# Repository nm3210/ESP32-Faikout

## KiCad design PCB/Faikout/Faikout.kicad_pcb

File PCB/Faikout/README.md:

# Faikout

## Trademark

This project is subject to the licence in the LICENCE file, and even if that says it is an open source project, you cannot sell boards or cases bearing the Andrews & Arnold Ltd name, the A&A logo, the registered trademark AJK logo or other registered trademarks, or any GS1 allocated EANs/barcode assigned to Andrews & Arnold Ltd.

## PCB Designs

These files are for use with [KiCAD](https://www.kicad.org).

- [Faikout](Faikout.kicad_pro)

## 3D

3D case designs are normally automatically created from the PCB so as to ensure correct details and placement of apertures, etc.

|Design|Bottom|Top|Combined|
|------|------|---|--------|
|Faikout||||

## PCB Images

---

*Auto generated README.md 2026-04-05T14:23:08*

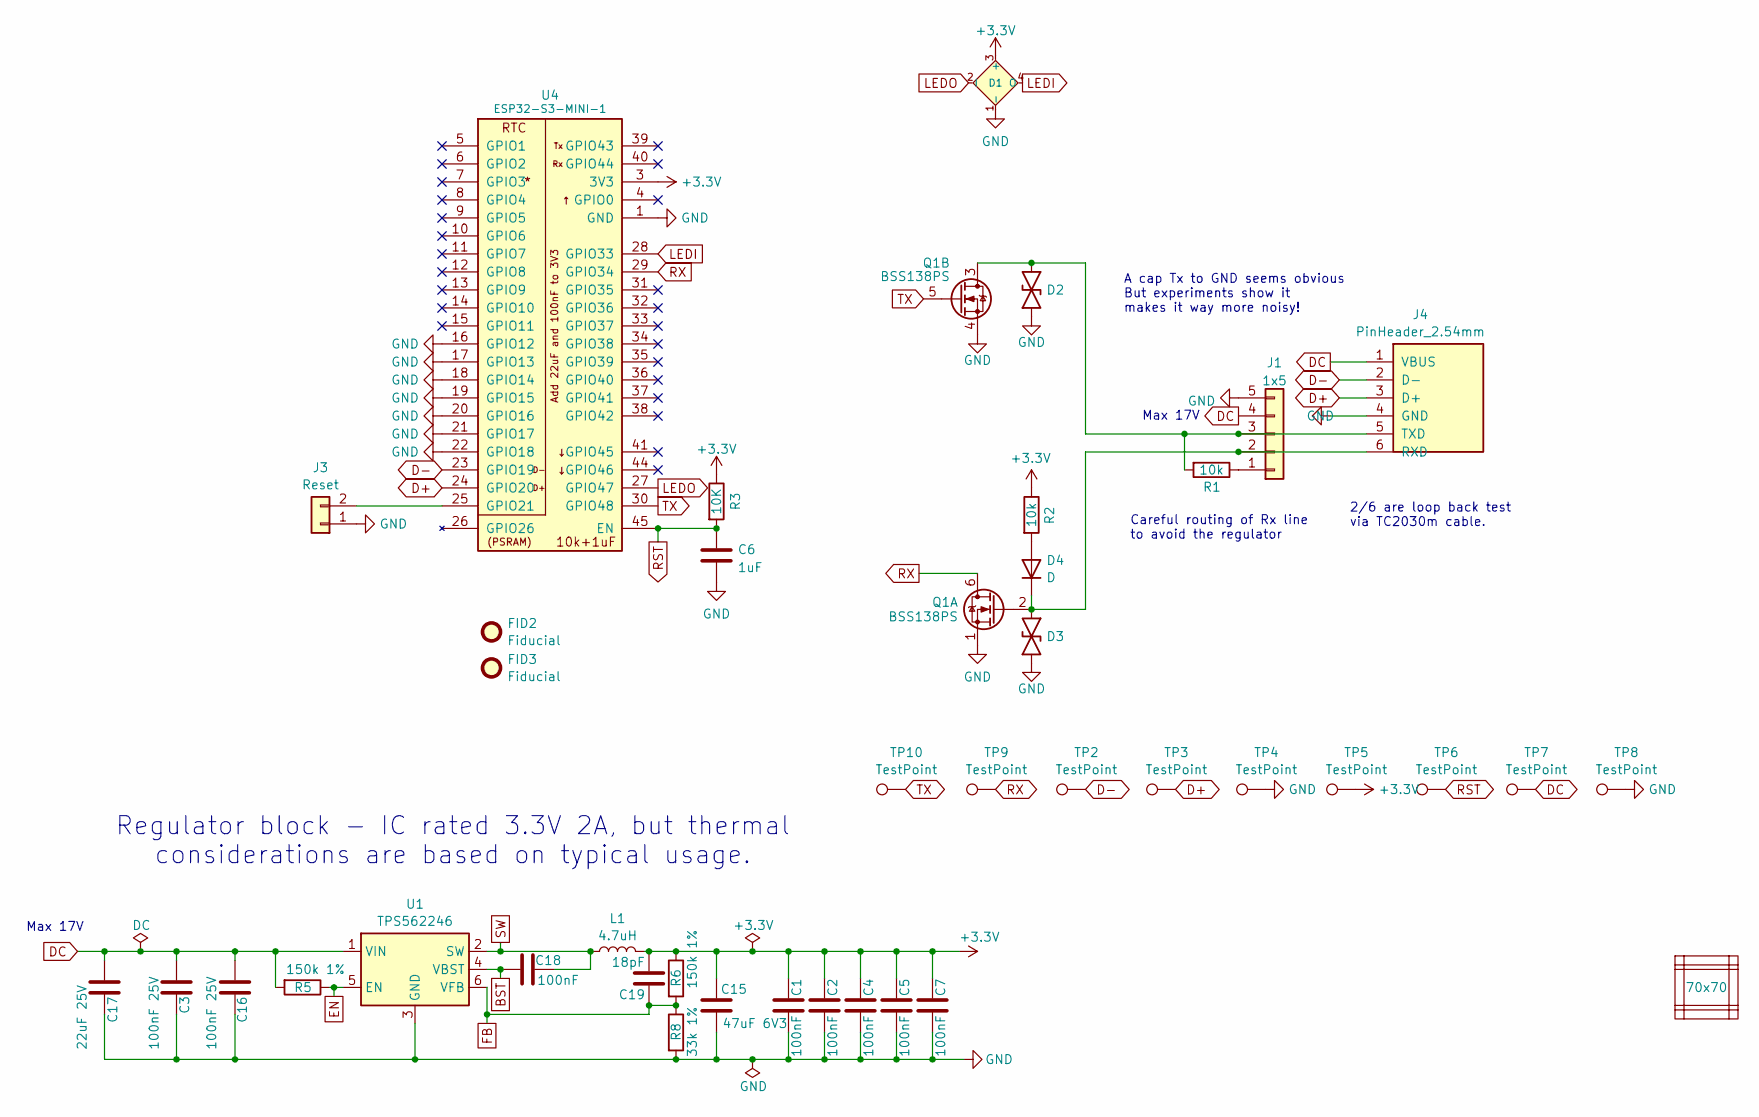
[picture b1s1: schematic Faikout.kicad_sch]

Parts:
C1, C2, C4, C5, C7, C18: 100nF; C_0201; MPN C76934
C3, C16: 100nF 25V; C_0402; MPN C56392
C6: 1uF; C_0201
C15: 47uF 6V3; C_0805; MPN C16780
C17: 22uF 25V; C_0805; MPN C45783
C19: 18pF; C_0201; MPN C62164
D1: XL-1615RGBC-2812B; SMD1615; MPN C5349954
D2, D3: DFN1006-2L; MPN C5137770
D4: D; D_0402; MPN C28642302
FID2, FID3: Fiducial; Fiducial_1mm_Mask2mm
J1: 1x5; JST_EH_S5B-EH_1x05_P2.50mm_Horizontal; MPN C265103
J3: Reset; AA-Pad
J4: PinHeader_2.54mm; PinHeader_1x06_P2.54mm_Vertical
L1: 4.7uH; L_5x5; MPN C307876
PCB1: 70x70; PCB7070
Q1: BSS138PS; SOT-363_SC-70-6; MPN C193381
R1, R2: 10k; R_0201; MPN C106225
R3: 10K; R_0201; MPN C106225
R5, R6: 150k 1%; R_0201; MPN C310173
R8: 33k 1%; R_0201; MPN C320835
TP2, TP3, TP4, TP5, TP6, TP7, TP8, TP9, TP10: TestPoint; PAD-2mm
U1: TPS562246; SOT-5x3-6; MPN C41833479
U4: ESP32-S3-MINI-1; MPN C3013941
V1, V2, V3, V4, V5, V6: VCUT70N

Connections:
+3.3V: C1.2, C2.2, C4.2, C5.2, C7.2, C15.1, C19.2, D1.3 (+), L1.2, R2.1, R3.1, R6.1, TP5.1, U4.3 (3V3)
BST: C18.1, U1.4 (VBST)
D+: J4.3 (D+), TP3.1, U4.24 (GPIO20); also elsewhere on the board
D-: J4.2 (D-), TP2.1, U4.23 (GPIO19); also elsewhere on the board
DC: C3.1, C16.1, C17.1, J1.4, J4.1 (VBUS), R5.2, TP7.1, U1.1 (VIN); also elsewhere on the board
EN: R5.1, U1.5 (EN)
FB: C19.1, R6.2, R8.1, U1.6 (VFB)
GND: C1.1, C2.1, C3.2, C4.1, C5.1, C6.2, C7.1, C15.2, C16.2, C17.2, D1.1 (-), D2.1, D3.1, J1.5, J3.1, J4.4 (GND), Q1.1 (SN), Q1.4 (DP), R8.2, TP4.1, TP8.1, U1.3 (GND), U4.1 (GND), U4.2 (GND), U4.16 (GPIO12), U4.17 (GPIO13), U4.18 (GPIO14), U4.19 (GPIO15), U4.20 (GPIO16), U4.21 (GPIO17), U4.22 (GPIO18), U4.42 (GND), U4.43 (GND), U4.46 (GND), U4.47 (GND), U4.48 (GND), U4.49 (GND), U4.50 (GND), U4.51 (GND), U4.52 (GND), U4.53 (GND), U4.54 (GND), U4.55 (GND), U4.56 (GND), U4.57 (GND), U4.58 (GND), U4.59 (GND), U4.60 (GND), U4.61 (GND), U4.62 (GND), U4.63 (GND), U4.64 (GND), U4.65 (GND); also elsewhere on the board
LEDI: D1.4 (O), U4.28 (GPIO33)
LEDO: D1.2 (I), U4.27 (GPIO47)
unnamed: D4.2 (A), R2.2
unnamed 11: D3.2, D4.1 (K), J1.2, J4.6 (RXD), Q1.2 (GN); also elsewhere on the board
unnamed: J1.1, R1.1
unnamed 13: D2.2, J1.3, J4.5 (TXD), Q1.3 (SP), R1.2; also elsewhere on the board
unnamed: J3.2, U4.25 (GPIO21)
RST: C6.1, R3.2, TP6.1, U4.45 (EN)
RX: Q1.6 (DN), TP9.1, U4.29 (GPIO34)
SW: C18.2, L1.1, U1.2 (SW)
TX: Q1.5 (GP), TP10.1, U4.30 (GPIO48)

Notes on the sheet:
Max 17V
Careful routing of Rx line to avoid the regulator
2/6 are loop back test via TC2030m cable.
A cap Tx to GND seems obvious But experiments show it makes it way more noisy!
Regulator block - IC rated 3.3V 2A, but thermal considerations are based on typical usage.

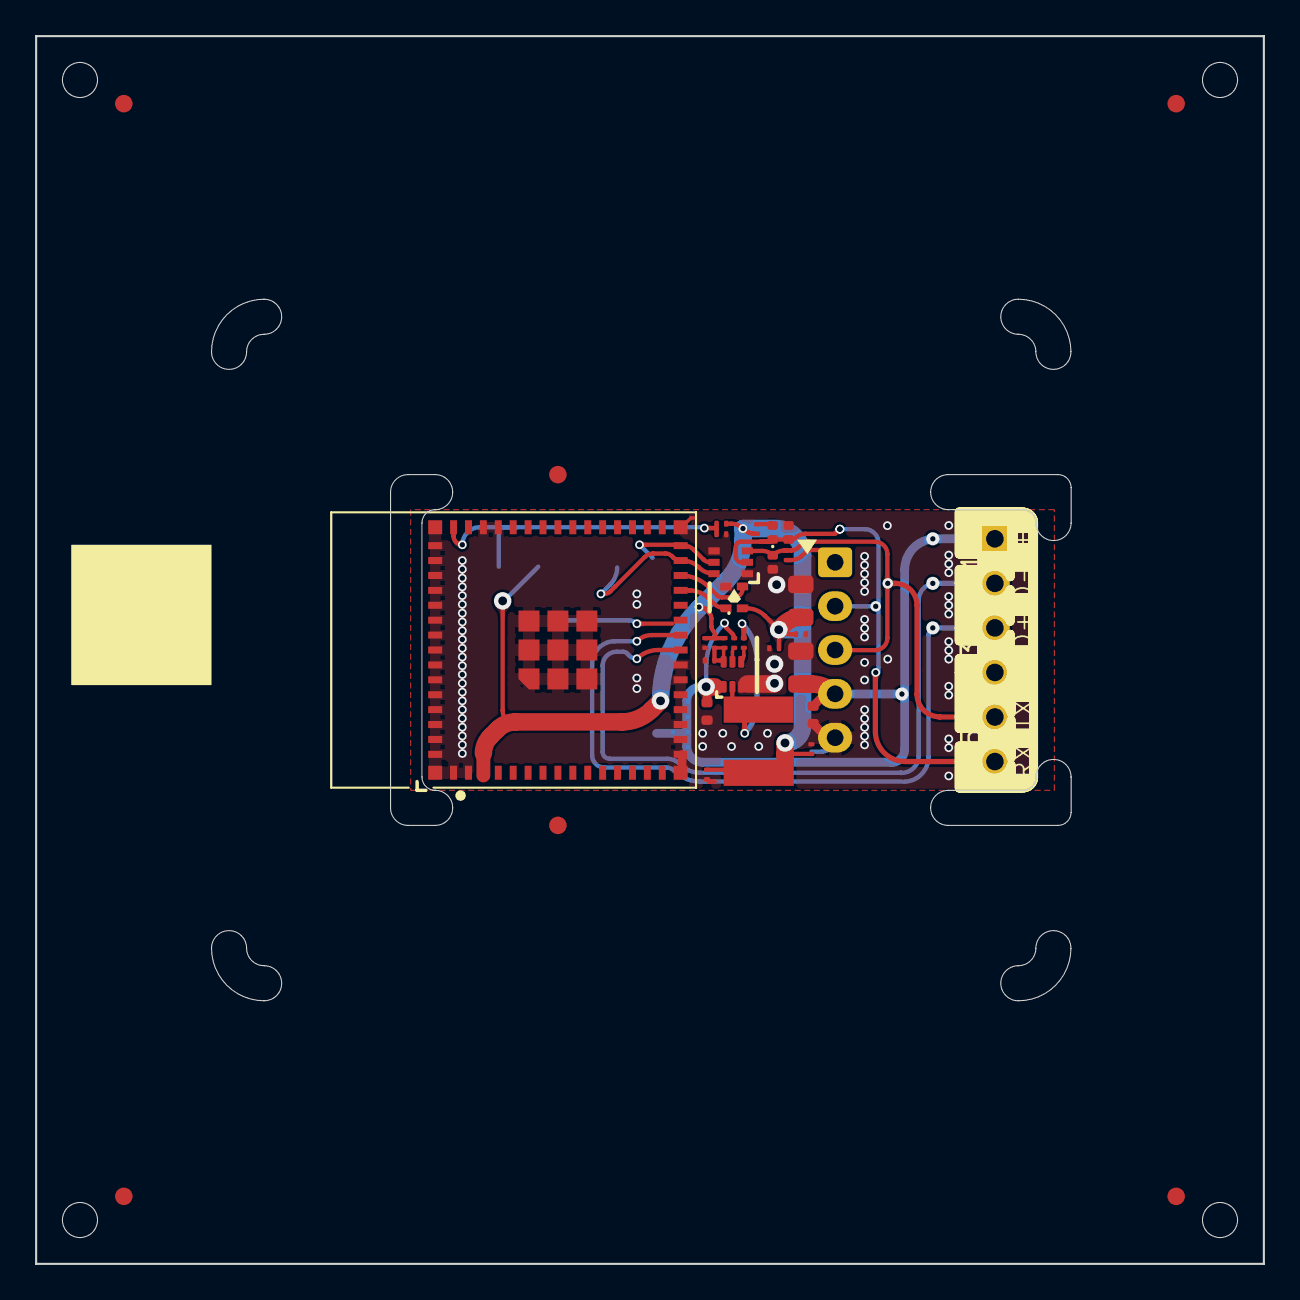
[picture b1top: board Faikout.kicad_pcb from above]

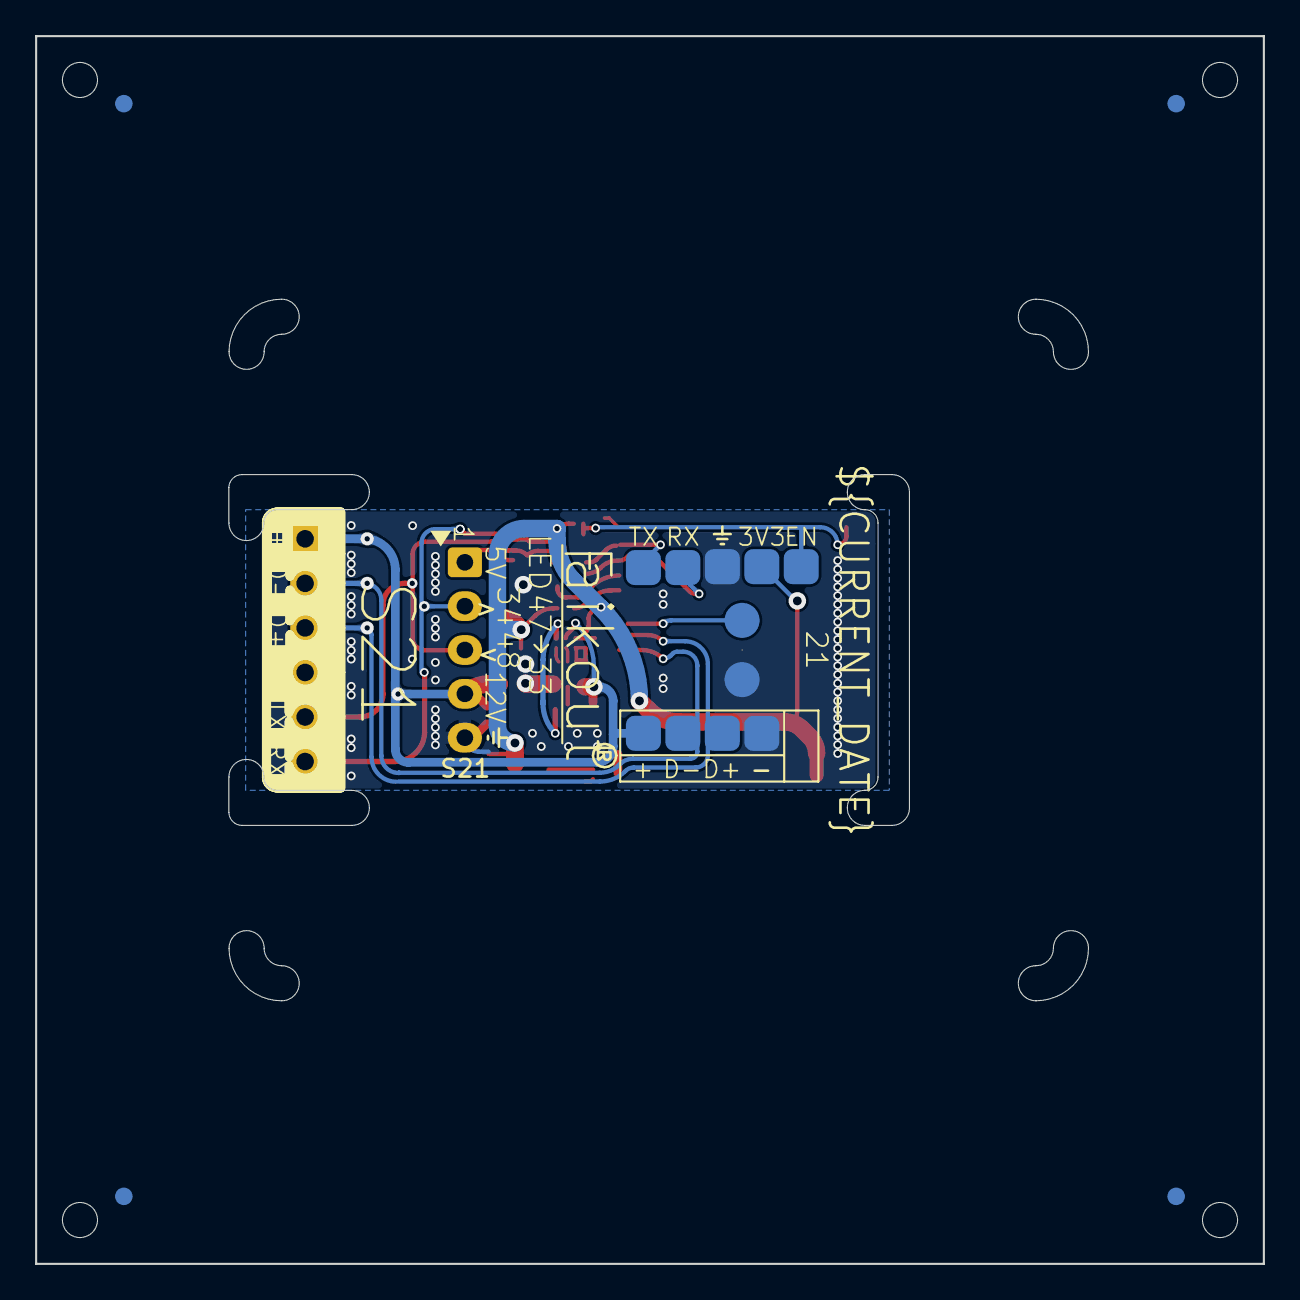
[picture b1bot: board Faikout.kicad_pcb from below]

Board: 2 copper layers, 70.0 x 70.0 mm, 47 parts (12 on the bottom side), 19 nets.

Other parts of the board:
J2: PinHeader_2.54mm; PinHeader_1x06_P2.54mm_Vertical

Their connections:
D+: J2.3 (D+); also elsewhere on the board
D-: J2.2 (D-); also elsewhere on the board
DC: J2.1 (VBUS); also elsewhere on the board
GND: J2.4 (GND); also elsewhere on the board
unnamed 11: J2.6 (RXD); also elsewhere on the board
unnamed 13: J2.5 (TXD); also elsewhere on the board

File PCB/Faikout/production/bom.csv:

Designator,Footprint,Quantity,Value,LCSC Part #
"C1, C18, C2, C4, C5, C7",C_0201,6,100nF,C76934
C15,C_0805,1,47uF 6V3,C16780
"C16, C3",C_0402,2,100nF 25V,C56392
C17,C_0805,1,22uF 25V,C45783
C19,C_0201,1,18pF,C62164
C6,C_0201,1,1uF,
D1,SMD1615,1,XL-1615RGBC-2812B,C5349954
"D2, D3",DFN1006-2L,2,~,C5137770
D4,D_0402,1,D,C28642302
J1,JST_EH_S5B-EH_1x05_P2.50mm_Horizontal,1,1x5,C265103
L1,L_5x5,1,4.7uH,C307876
Q1,SOT-363_SC-70-6,1,BSS138PS,C193381
"R1, R2, R3",R_0201,3,10k,C106225
"R5, R6",R_0201,2,150k 1%,C310173
R8,R_0201,1,33k 1%,C320835
U1,SOT-5x3-6,1,TPS562246,C41833479
U4,ESP32-S3-MINI-1,1,ESP32-S3-MINI-1-N4R2,C3013941

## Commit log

2026-03-09 Not github
2026-03-09 Beta
2026-03-10 Local images
2026-03-10 Typo
2026-03-10 Tidy
2026-03-10 Links?
2026-03-10 Cleaner web startup
2026-03-10 Tidy up
2026-03-11 Render update
2026-03-21 KiCAD 10
2026-03-22 Label max voltage
2026-03-22 Voltage
2026-03-27 Release
2026-03-27 Connector
2026-04-02 Allow F9 to work if no RH/Ra
2026-04-03 C3 build, and fix memset
2026-04-03 Restart HA
2026-04-03 Library update
2026-04-06 Silkscreen tidy
2026-04-08 reset button
2026-04-10 Fix mobile overflow on Auto target temperature slider
    input.temp used min-width:230px which forced the inner auto-section
    table wider than the viewport on narrow mobile browsers. Replace with
    width:100%;max-width:230px so the slider shrinks on small screens.
    Also add width=100% to the inner table so the slider width resolves
    against a bounded container.
2026-05-03 Lectronz
2026-05-11 Revert change as too small on many screens now.
2026-05-14 Tweak
2026-05-14 nofaikoutauto HA switch
2026-05-14 More HA switch/setting controls
2026-05-14 more checks
2026-05-19 Remove logos & update the PCB to use 1x6 header instead of TC2030
    Transitioned the programming interface to a more standard pin header and removed branding elements to make the project more open-source friendly.
    * Programming Header (J2):
    * Replaced the TC2030 (Tag-Connect) interface with a standard 1x06 2.54mm vertical pin header.
    * Updated the footprint to Connector_PinHeader_2.54mm:PinHeader_1x06_P2.54mm_Vertical.
    * Updated schematic symbols and adjusted routing for the new header pinout (D+, D-, DC, and GND).
    * Updated schematic annotations to refer to "programming cable" instead of "TC2030m".
